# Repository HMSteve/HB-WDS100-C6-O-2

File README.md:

# HB-WDS100-C6-O-2

Ein "Reparaturset" fuer den Wetter-Kombisensor HM-WDS100-C6-O-2 auf Basis der AskSinPP-Bibliothek. Da Ausfaelle des originalen Wetter-Kombisensors wegen Korrosion der Hauptplatine offenbar nach einigen Jahren haeufiger vorkommen, die eigentliche Mechanik des Geraetes jedoch langlebig erscheint, wurde eine Ersatz-Elektronik sowie AskSinPP-basierte Firmware entwickelt, die es erlaubt, den Sensor ohne Modifikationen oder Addon-Installationen auf der CCU wieder zum Leben zu erwecken. Dazu sind sowohl die Hauptplatine als auch die Windrichtungsmesserplatine gegen die neu konzipierten Platinen auszutauschen und der Sensor neu anzulernen.

## Hardware

### Demontage des Kombisensors

Die Demontage des die Hauptplatine (und Batteriefach sowie Anemometer) tragenden Geraeteteils muss vorsichtig in folgenden Schritten erfolgen, um Schaeden an den Plastikteilen zu vermeiden:
1. Gehaeusehuelse ueber dem Batteriefach oeffnen und Batterien entfernen, Westernstecker loesen.
2. Beide Schrauben, die den Rotor mit den drei Schalen auf der Welle halten, leicht loesen und Rotor abziehen.
3. Zwei unter der Rotorkappe sichtbarwerdende vierkantige Arretierungsstifte aus Platik vorsichtig nach oben herausziehen (etwas mit dem Schraubenzieher hebeln, dann mit der Zange greifen und senkrecht herausziehen)
4. Die drei Ringe zum Sonnen- und Wetterschutz (Stevenson-Screen) mit dem oberen beginnend leicht im Urzeigersinn drehen, dass sich der jeweilige Bajonettverschluss loest, und Ring senkrecht nach oben abziehen.
5. Zwei kleine Schrauben ganz oben am Lager der Welle sowie danach fuenf lange Gehaeuseschrauben entfernen.
6. Zwei Schrauben, die den Aufbau auf dem Edelstahlrohr fixieren, loesen und Aufbau senkrecht nach oben aus dem Rohr Heraus ziehen
7. Die beiden Gehaeusehalbschalen lassen sich nun trennen und die defekte Platine ausbauen. Die Kabel koennen in der anderen Gehaeusehalbschale verbleiben.

Die Demontage der Windrichtungsmesserplatine ist unproblematisch.

### Ersatzplatinen

Als Ersatz sind zwei neue Platinen herzustellen: [Schalt- und Bestueckungsplaene sowie Gerberfiles](https://github.com/HMSteve/HB-WDS100-C6-O-2/tree/main/PCB).

Die Platinen sind bzgl. Bauteilbauformen, Padgroessen und Abstaenden grundsaetzlich fuer Handloetung vorgesehen, Details siehe unten.

Fuer die etwas spezielleren Bauteile finden sich Bezugsquellen hier: [Bezugsquellen](https://github.com/HMSteve/HB-WDS100-C6-O-2/tree/main/PCB/SourcingSpecialParts.xlsx)

### Hauptplatine

Die Platine basiert auf einem ATMega1284p. Die Temperatur-/Luftfeuchtemessung erfolgt mit einem SHT31, die Helligkeitsmessung mit einem [VEML6030](https://github.com/HMSteve/HB-WDS100-C6-O-2/blob/main/datasheets/VEML6030.pdf). Die Windgeschwindigkeit wird wie im Original per Reedkontakt gezaehlt, zur Reduzierung des Stromverbrauchs wird zum Zaehlen ein [PCF8593](https://github.com/HMSteve/HB-WDS100-C6-O-2/blob/main/datasheets/PCF8593.pdf) eingesetzt.

Ein paar Fotos vom Aufbau:

Bei Bestueckung der als Layout und Gerberfiles vorliegenden Platine v2.0 sind zwei Fehler zu korrigieren. Dazu ist jeweils etwas Loetstoplack zu entfernen, um die geaenderten Bauteilpostionen bestuecken zu koennen.

1. C17 ist nicht direkt am CC1101-Modul zu bestuecken, sondern direkt vor dem FET zur Abschaltung der Betriebsspannung bzw. an der dort vorhandenen Durchkontaktierung gegen die Masseflaeche. Ohne diese Aenderung koennen die Einschaltstromspitzen zu einem Brownout des ATMega fuehren und die Schaltung laeuft nicht oder geraet in eine Reset-Schleife.
2. Der markierte 3.3M-Pullup-Widerstand gegen 3.3V fehlt im Layout und ist wie gezeigt zu ergaenzen. Auf Grund der Konstruktion der Regenzaehlerwippe, deren Reedkontakt in einer stabilen Wippenstellung stets geschlossen ist, scheidet die Nutzung des niederohmigen internen pull-up des ATMega wegen des Energieverbrauchs aus.

Der korrigierte [Schaltplan v2.1](https://github.com/HMSteve/HB-WDS100-C6-O-2/blob/main/PCB/HB-WDS100-C6-O-2_Main_v2p1Schematic.pdf) (ohne Platinenlayout-Aenderung) zeigt die korrekte Schaltung.

Zunaechst sind alle Bauteile ausser dem SHT31 zu bestuecken und die Platine bspw. mit Isopropanol von Flussmittelresten zu reinigen. Ganz zum Schluss wird der SHT31 bestueckt und die Schutzkappe aufgesetzt. Der Sensor darf Loesungsmitteln nicht ausgesetzt werden.

Waehrend die Bestueckung und Loetung von Hand fuer fast alle Bauteile unproblematisch ist, gestaltet sich die Handloetung des SHT31 und VEML6030 aber etwas schwieriger. Mit Lupenbrille oder Mikroskop und geregeltem Loetkolben mit guter Spitze ist dies moeglich. Empfehlenswerter ist jedoch Reflowloeten, wobei die Sensoren nicht von oben mit Heissluft oder Infrarotstrahlung erhitzt werden sollten. Da die Platinenunterseite unter den Sensoren frei ist, bietet sich Erhitzung von unten mit Heissluft hat. Das Auftragen der Lotpaste wird mittels Schablone stark vereinfacht - Standardschablonen sind bspw. bei [Proto-Advantage](https://www.proto-advantage.com/) erhaeltlich.

Der besonders der Witterung ausgesetzte schmale (obere) Teil der Platine sollte wenn moeglich dennoch mittels Schutzlack geschuetzt werden, um die Witterungsbestaendigkeit zu erhoehen. Auch hierbei ist der SHT31 vor Loesungsmitteln zu schuetzen, bspw. durch Aufpinseln statt Spruehen von [FSC](https://electrolube.com/product/fsc-flexible-silicone-conformal-coating/) auf die Platine, nicht jedoch auf die Schutzkappe des Sensors, und Trocknung in einem gut beluefteten warmen Raum.

Beim Einbau der Platine in das Gehaeuse sollte die Aussparung, durch die der schmale Platinenteil sowie der Antennendraht gefuehrt werden, beidseitig wie im Foto zu sehen mit neutral vernetzendem Silikon abgedichtet werden.

### Windrichtungsmesserplatine

Auch wenn die Original-Windrichtungsmesserplatine kaum korrosionsanfaellig montiert und vermutlich nicht defekt ist, wurde zur einfacheren Einbindung in die gewaehlte AVR-Erchitektur auch diese neu erstellt. Genutzt wird ein [AS5600](https://github.com/HMSteve/HB-WDS100-C6-O-2/blob/main/datasheets/AS5600.pdf) Halleffekt-Drehwinkelsensor, der ueber einen FET auf der Hauptplatine zwischen den Messungen zur Verringerung des Stromverbrauchs abgeschaltet wird.

Der Aufbau erfolgt ohne Besonderheiten. Der Loetjumper SJ1 ist entsprechend dem Foto gegen Masse zu schliessen.

## Firmware

Zur Verwendung des ATMega1284p ist bei Nutzung der Arduino IDE zunaechst eine zusaetzliche sog. Boardverwalter-URL (https://mcudude.github.io/MightyCore/package_MCUdude_MightyCore_index.json) in den Voreinstellungen zu hinterlegen. Folgende Boardeinstellungen sind dann auszuwaehlen:

Danach kann der Bootloader geflashed werden.

Sollte versehentlich externer Takt oder Quarzoszillator eingestellt oder die entsprechenden Fuses anderweitig falsch gesetzt worden sein, kann auf der Platine ein 8MHz-Resonator CSTNE von Murata bestueckt werden, um den Controller zu retten. Fuer den Normalbetrieb ist der Resonator nicht notwendig.

Um die [Firmware](https://github.com/HMSteve/HB-WDS100-C6-O-2/tree/main/Firmware)  zu kompilieren, muessen sich die .ino sowie die .h Dateien im gleichen Verzeichnis befinden, das ./sensors-Verzeichnis darunter. Zudem muss eine Reihe von Bibliotheken ueber den Library Manager eingebunden werden:
- AskSinPP
- EnableInterrupt
- LowPower
- Adafruit_SHT31 Arduino Library
- PCF8583 Library (Diese wird hier fuer den stromsparenderen PCF8593 genutzt.)

Anschliessend sollte die Firmware problemlos kompilierbar und das Device nach dem Flashen anlernbar sein.

## Bedienung

Die Bedienung erfolgt grundsaetzlich analog dem originalen HM-WDS100-C6-O-2. Der Sensor kann an eine CCU angelernt werden. Direktverknuepfungen zum Steuerun von Aktoren abhaengig von der Windgeschwindigkeit sind moeglich. Lediglich der Live Mode ist nicht implementiert.

### Geraetetaste

Die Geraetetaste weist folgende Funktionen auf:
- kurzer Druck: Anlernmodus starten / Konfiguration uebernehmen (LED langsam rot blinkend)
- langer Druck: Einnordungsmodus starten (kurzes Blinkmuster der roten LED)
- sehr langer Druck: Zuruecksetzen auf Werkseinstellung (einmaliges Aufleuchten der gruenen LED)

### Einnorden

Bei Erstinstallation nach Montage ist der Einnordungsmodus durch langen Druck der Geraetetaste zu starten, die Windfahne Richtung Norden auszurichten und so festzuhalten und sodann die Geraetetaste kurz zu druecken. Das Abspeichern des absoluten Winkels der Nordrichtung im EEPROM wird durch Aufleuchten der gruenen LED bestaetigt. Erfolgt dies nicht, ist der Vorgang zu wiederholen.

### Helligkeit und Windgeschwindigkeit

Um den geringen Dynamikumfang des Originalsensors etwas zu verbessern und insbesondere Helligkeiten in der Daemmerung sinnvoll auswerten zu koennen, wird die Beleuchtungsstaerke in Lux logarithmiert und auf den 8-Bit-Wertebereich skaliert ausgegeben. 100 kLux entsprechen etwa einem Wert von 220, 100 Lux noch immer etwa einem Wert von 80.

Die Windgeschwindigkeit wurde mit Hausmitteln (Hand-Schalenanemometer und Laubblasgeraet) kalibriert, bei 35 Messungen ergab sich eine Regression mit Bestimmtheitsmass 0.9. Im Gegensatz zum Originalsensor werden auch hoehere Windgeschwindigkeiten noch gemessen.

### Hinweise zum Energieverbrauch

Die mittlere Stromaufnahme des Sensors bei einem Sendeintervall von etwa 3 Minuten betraegt knapp 30uA, so dass eine Batterielaufzeit von einigen Jahren erreichbar sein sollte.  

## Disclaimer

Die Nutzung der hier veroeffentlichten Inhalte erfolgt vollstaendig auf eigenes Risiko und ohne jede Gewaehr.

## Lizenz

**Creative Commons BY-NC-SA**<br>
Give Credit, NonCommercial, ShareAlike

<br />This work is licensed under a <a rel="license" href="http://creativecommons.org/licenses/by-nc-sa/4.0/">Creative Commons Attribution-NonCommercial-ShareAlike 4.0 International License</a>.

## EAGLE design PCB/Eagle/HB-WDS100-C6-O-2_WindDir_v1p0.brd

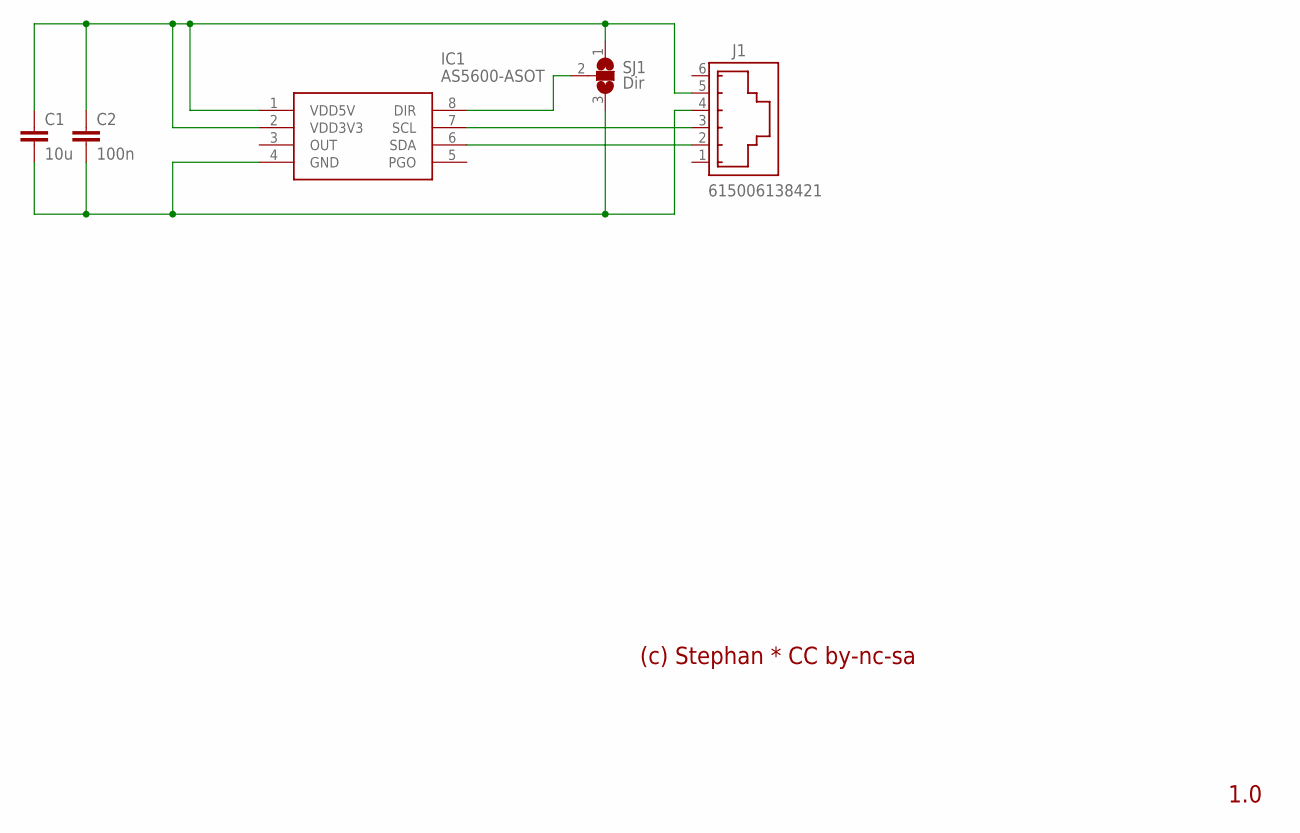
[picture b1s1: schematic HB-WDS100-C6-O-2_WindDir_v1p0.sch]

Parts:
C1: 10u; C0805K
C2: 100n; C0805K
IC1: AS5600-ASOT; SOIC127P600X175-8N
J1: 615006138421
SJ1: Dir; SJ_2

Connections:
3V3: C1.1, C2.1, IC1.1 (VDD5V), IC1.2 (VDD3V3), J1.5, SJ1.1
DIR: IC1.8 (DIR), SJ1.2
GND: C1.2, C2.2, IC1.4 (GND), J1.4, SJ1.3
SCL: IC1.7 (SCL), J1.3
SDA: IC1.6 (SDA), J1.2

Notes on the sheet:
(c) Stephan * CC by-nc-sa
1.0

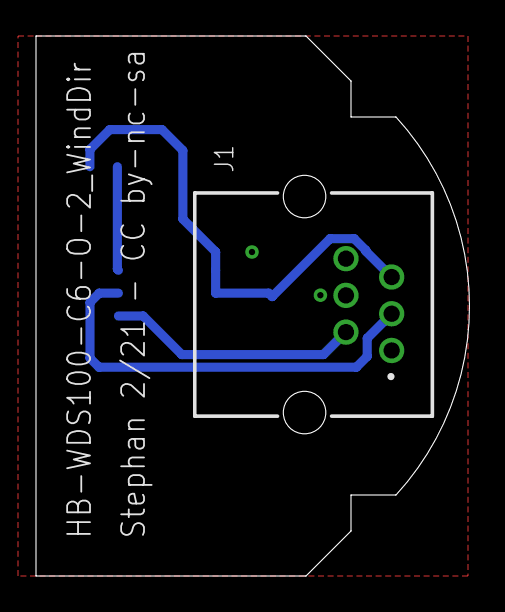
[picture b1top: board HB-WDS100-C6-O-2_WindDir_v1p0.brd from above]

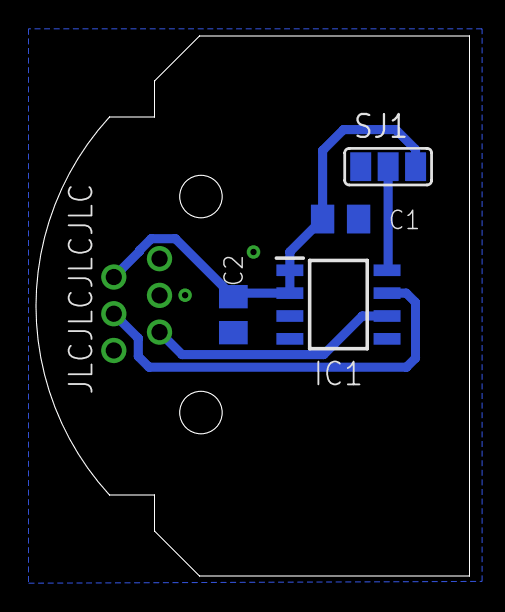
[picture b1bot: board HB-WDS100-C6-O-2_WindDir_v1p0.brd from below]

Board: 2 copper layers, 24.1 x 30.0 mm, 5 parts (4 on the bottom side), 5 nets.

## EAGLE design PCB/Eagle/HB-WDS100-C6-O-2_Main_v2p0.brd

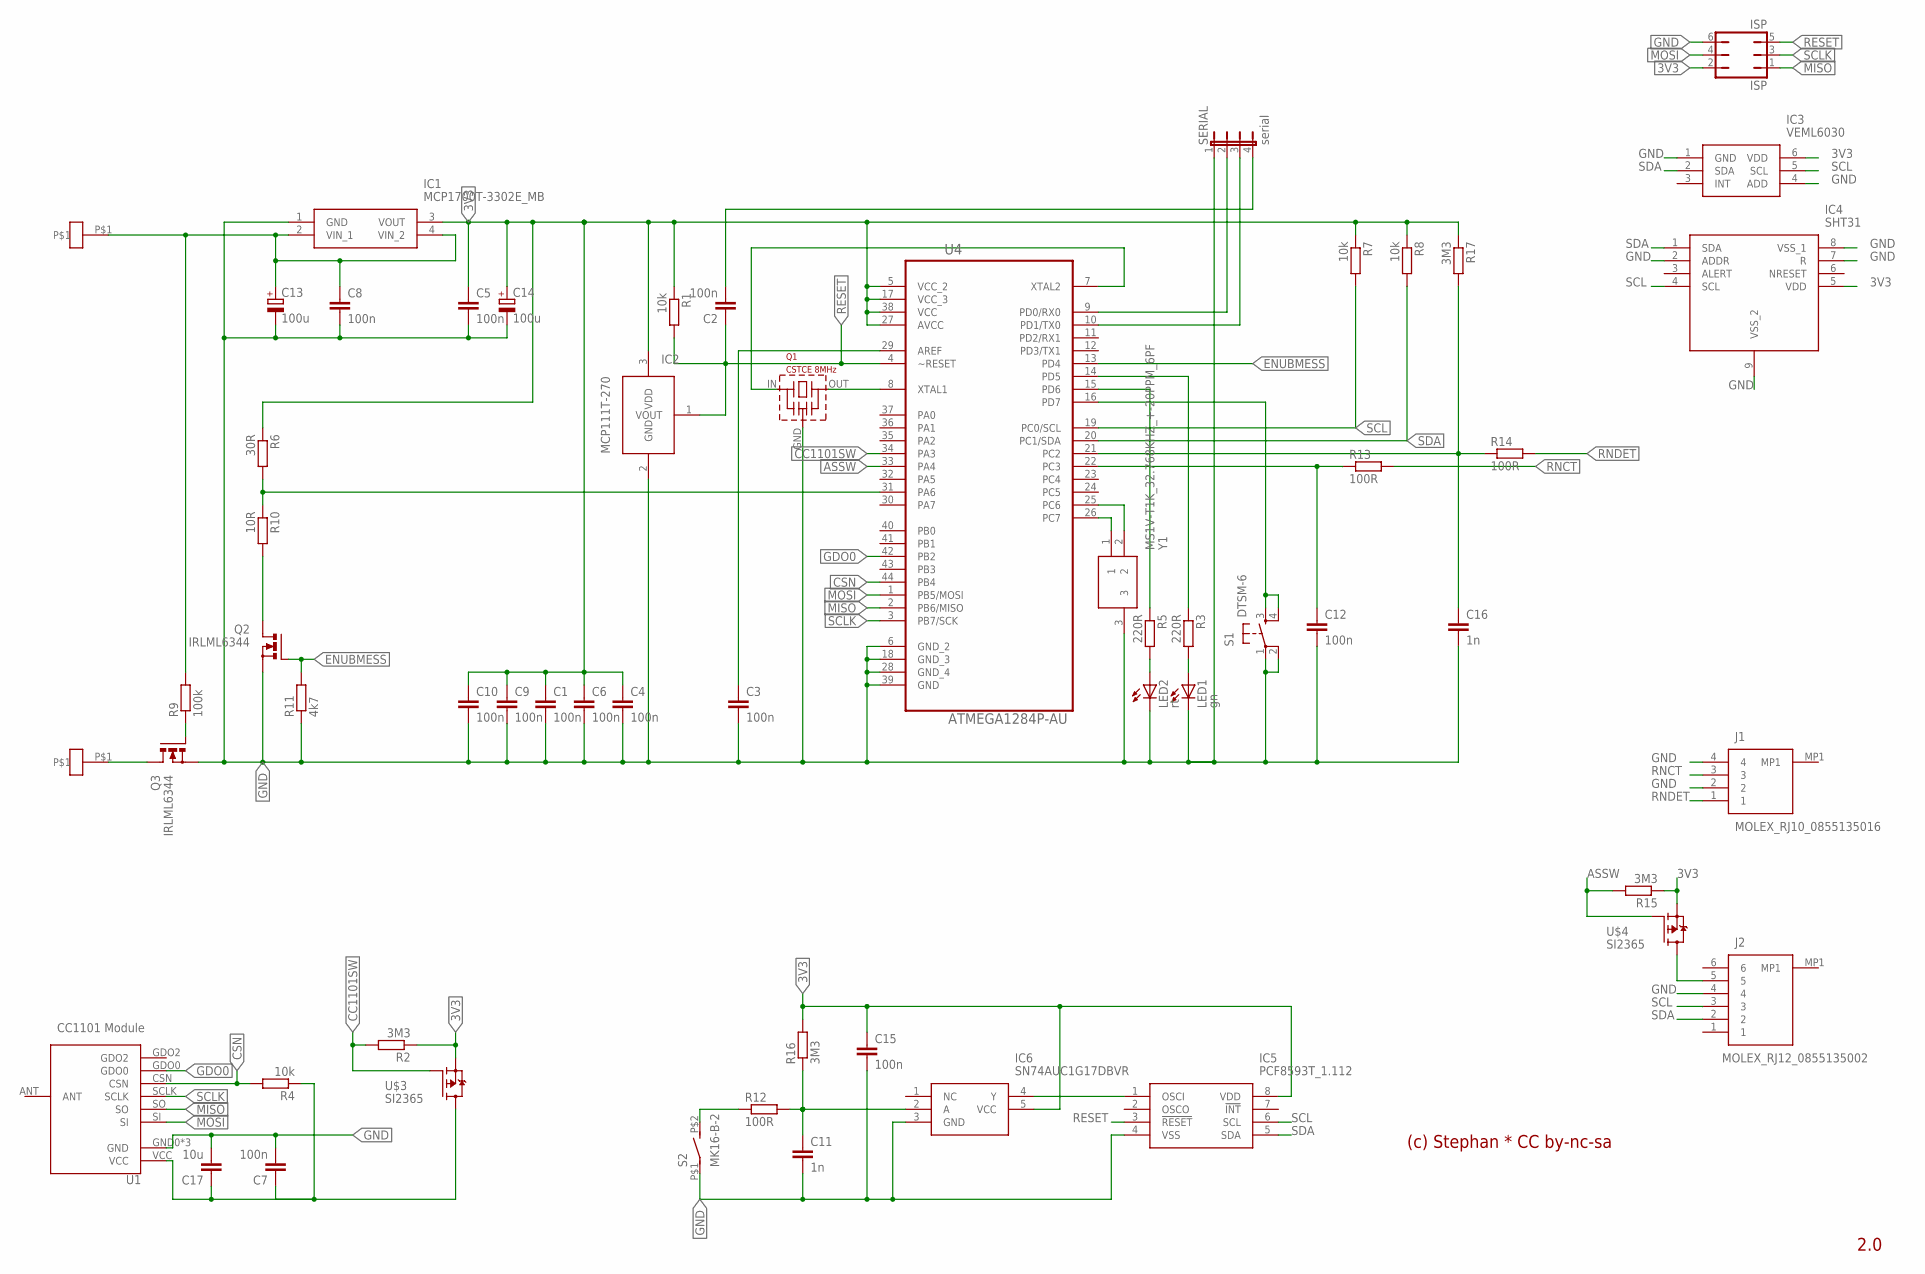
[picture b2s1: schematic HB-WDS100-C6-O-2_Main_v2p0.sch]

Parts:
C1, C2, C3, C4, C5, C6, C7, C8, C9, C10, C12, C15: 100n; C0805K
C11, C16: 1n; C0805K
C13, C14: 100u; CT3528
C17: 10u; C0805K
IC1: MCP1700T-3302E_MB; MCP1700T-3302E/MB
IC2: MCP111-270; SOT23
IC3: VEML6030; VEML6030-HANDSOLD
IC4: SHT31; SON50P250X250X90-9N-HANDSOLD
IC5: PCF8593T_1.112; SOIC127P600X175-8N
IC6: SN74AUC1G17DBVR; SOT95P280X145-5N
ISP: ISP; JP3Q
J1: MOLEX_RJ10_0855135016
J2: MOLEX_RJ12_0855135002
LED1: gn; CHIPLED_0805
LED2: rt; CHIPLED_0805
Q1: CSTCE 8MHz; CSTCE
Q2, Q3: IRLML6344; SOT-23
R1, R4, R7, R8: 10k; R0805W
R2, R15, R16, R17: 3M3; R0805W
R3, R5: 220R; R0805W
R6: 30R; R0805W
R9: 100k; R0805W
R10: 10R; R0805W
R11: 4k7; R0805W
R12, R13, R14: 100R; R0805W
S1: DTSM-6
S2: MK16-B-2
SERIAL: serial; JP4
U1: CC1101CC1101-SMD-2MM; CC1101-SMD2MM
U4: ATMEGA1284P-AU; QFP80P1200X1200X120-44N
U$1, U$2: LOETOESE
U$3, U$4: SI2365; SOT23
Y1: MS1V-T1K_32.768KHZ_+-20PPM_6PF; MS1VT1K32768KHZ20PPM6PF

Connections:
3V3: C1.1, C4.1, C5.1, C6.1, C9.1, C10.1, C14.+, C15.1, IC1.3 (VOUT), IC2.3 (VDD), IC3.6 (VDD), IC4.5 (VDD), IC5.8 (VDD), IC6.5 (VCC), ISP.2, R1.1, R2.1, R6.1, R7.1, R8.1, R15.1, R16.2, R17.1, U4.5 (VCC_2), U4.17 (VCC_3), U4.27 (AVCC), U4.38 (VCC), U$3.2 (S), U$4.2 (S)
3V3AS5600: J2.5, U$4.3 (D)
3V3CC1101: C7.1, C17.1, R4.1, U1.VCC, U$3.3 (D)
AREF: C3.1, U4.29 (AREF)
ASSW: R15.2, U4.33 (PA4), U$4.1 (G)
BATTMINUS: Q3.P3 (D), U$2.P$1
CC1101SW: R2.2, U4.34 (PA3), U$3.1 (G)
CSN: R4.2, U1.CSN, U4.44 (PB4)
ENUBMESS: Q2.P1 (G), R11.2, U4.13 (PD4)
GDO0: U1.GDO0, U4.42 (PB2)
GND: C1.2, C3.2, C4.2, C5.2, C6.2, C7.2, C8.2, C9.2, C10.2, C11.2, C12.2, C13.-, C14.-, C15.2, C16.2, C17.2, IC1.1 (GND), IC2.2 (GND), IC3.1 (GND), IC3.4 (ADD), IC4.2 (ADDR), IC4.7 (R), IC4.8 (VSS_1), IC4.9 (VSS_2), IC5.4 (VSS), IC6.3 (GND), ISP.6, J1.2, J1.4, J2.4, LED1.C, LED2.C, Q1.GND, Q2.P2 (S), Q3.P2 (S), R11.1, S1.1, S1.2, S2.P$1, SERIAL.1, U1.GND0 (GND), U1.GND1 (GND), U1.GND2 (GND), U4.6 (GND_2), U4.18 (GND_3), U4.28 (GND_4), U4.39 (GND), Y1.3
LED1: LED1.A, R3.2
LED1R: R3.1, U4.14 (PD5)
LED2: LED2.A, R5.2
LED2R: R5.1, U4.15 (PD6)
MISO: ISP.1, U1.SO, U4.2 (PB6/MISO)
MOSI: ISP.4, U1.SI, U4.1 (PB5/MOSI)
OSC1: U4.25 (PC6), Y1.2
OSC2: U4.26 (PC7), Y1.1
PCFIN: IC5.1 (OSCI), IC6.4 (Y)
Q3GATE: Q3.P1 (G), R9.1
REEDSW: R12.1, S2.P$2 (S)
RESET: C2.1, IC2.1 (VOUT), IC5.3 (!RESET), ISP.5, R1.2, U4.4 (~RESET)
RNCT: J1.3, R13.2
RNCTPIN: C12.1, R13.1, U4.22 (PC3)
RNDET: J1.1, R14.2
RNDETPIN: C16.1, R14.1, R17.2, U4.21 (PC2)
RX: SERIAL.2, U4.9 (PD0/RX0)
SCL: IC3.5 (SCL), IC4.4 (SCL), IC5.6 (SCL), J2.3, R7.2, U4.19 (PC0/SCL)
SCLK: ISP.3, U1.SCLK, U4.3 (PB7/SCK)
SDA: IC3.2 (SDA), IC4.1 (SDA), IC5.5 (SDA), J2.2, R8.2, U4.20 (PC1/SDA)
SERIALRESET: C2.2, SERIAL.4
STIN: C11.1, IC6.2 (A), R12.2, R16.1
SW1: S1.3, S1.4, U4.16 (PD7)
TX: SERIAL.3, U4.10 (PD1/TX0)
UBATT: C8.1, C13.+, IC1.2 (VIN_1), IC1.4 (VIN_2), R9.2, U$1.P$1
UBMESS: R6.2, R10.1, U4.31 (PA6)
VOLTDEVFOOT: Q2.P3 (D), R10.2
XTAL1: Q1.OUT, U4.8 (XTAL1)
XTAL2: Q1.IN, U4.7 (XTAL2)

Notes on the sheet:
MCP111T-270
(c) Stephan * CC by-nc-sa
2.0
CC1101 Module

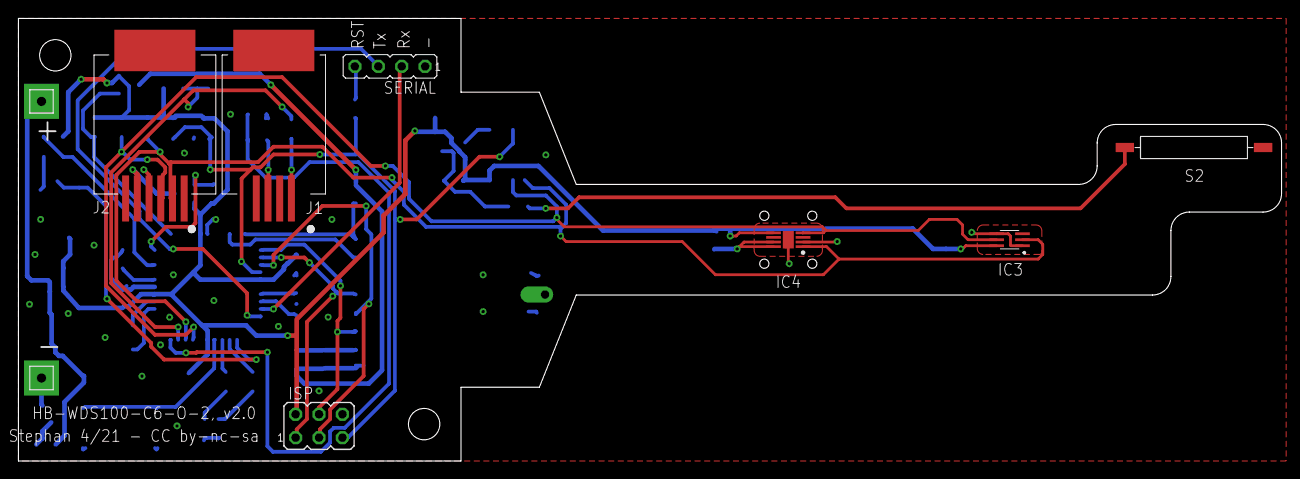
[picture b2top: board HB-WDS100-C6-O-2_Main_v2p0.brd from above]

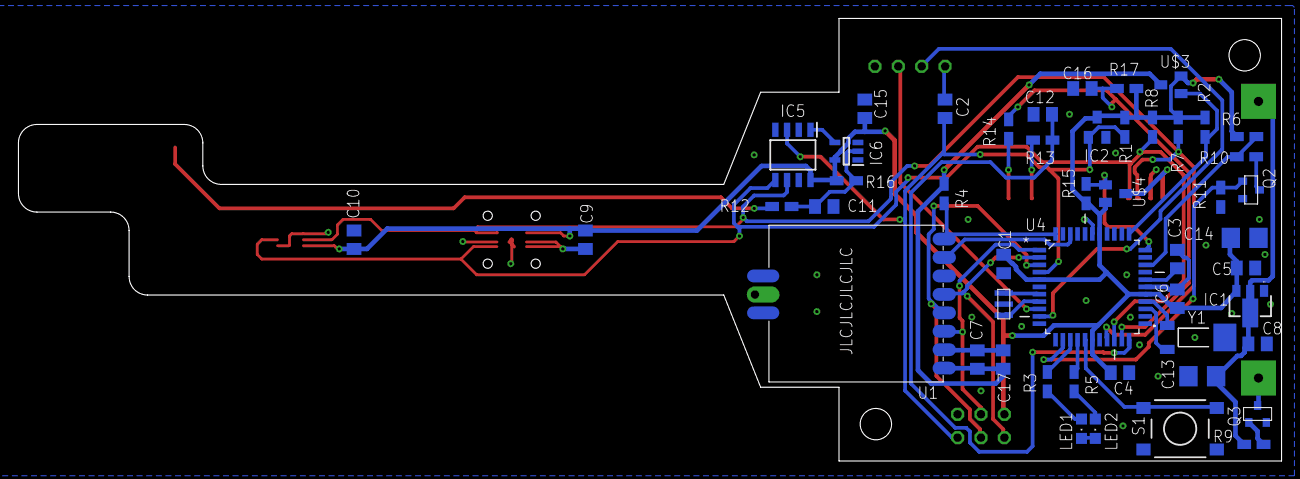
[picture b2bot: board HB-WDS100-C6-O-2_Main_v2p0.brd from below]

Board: 2 copper layers, 137.0 x 48.0 mm, 58 parts (49 on the bottom side), 40 nets.

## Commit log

2021-05-15 new version
2021-05-15 implemented cycleInfoMsgDis
2021-05-22 anemometer calib added
2021-05-23 pcb added
2021-05-23 edit imgs
2021-05-23 image added
2021-05-23 schematic v2.1 added
2021-05-30 Direktverknuepfungen ergaenzt
2021-06-10 BOM added
2024-01-03 Eagle files added

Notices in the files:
PCB/Eagle/HB-WDS100-C6-O-2_Main_v2p0.brd:
Stephan 4/21 - CC by-nc-sa
PCB/Eagle/HB-WDS100-C6-O-2_WindDir_v1p0.brd:
Stephan 2/21 - CC by-nc-sa
parts and their libraries:
modules: Released under the Creative Commons Attribution 4.0 International License: http://creativecommons.org/licenses/by/4.0
WuerthModular: Copyright: Würth Elektronik
